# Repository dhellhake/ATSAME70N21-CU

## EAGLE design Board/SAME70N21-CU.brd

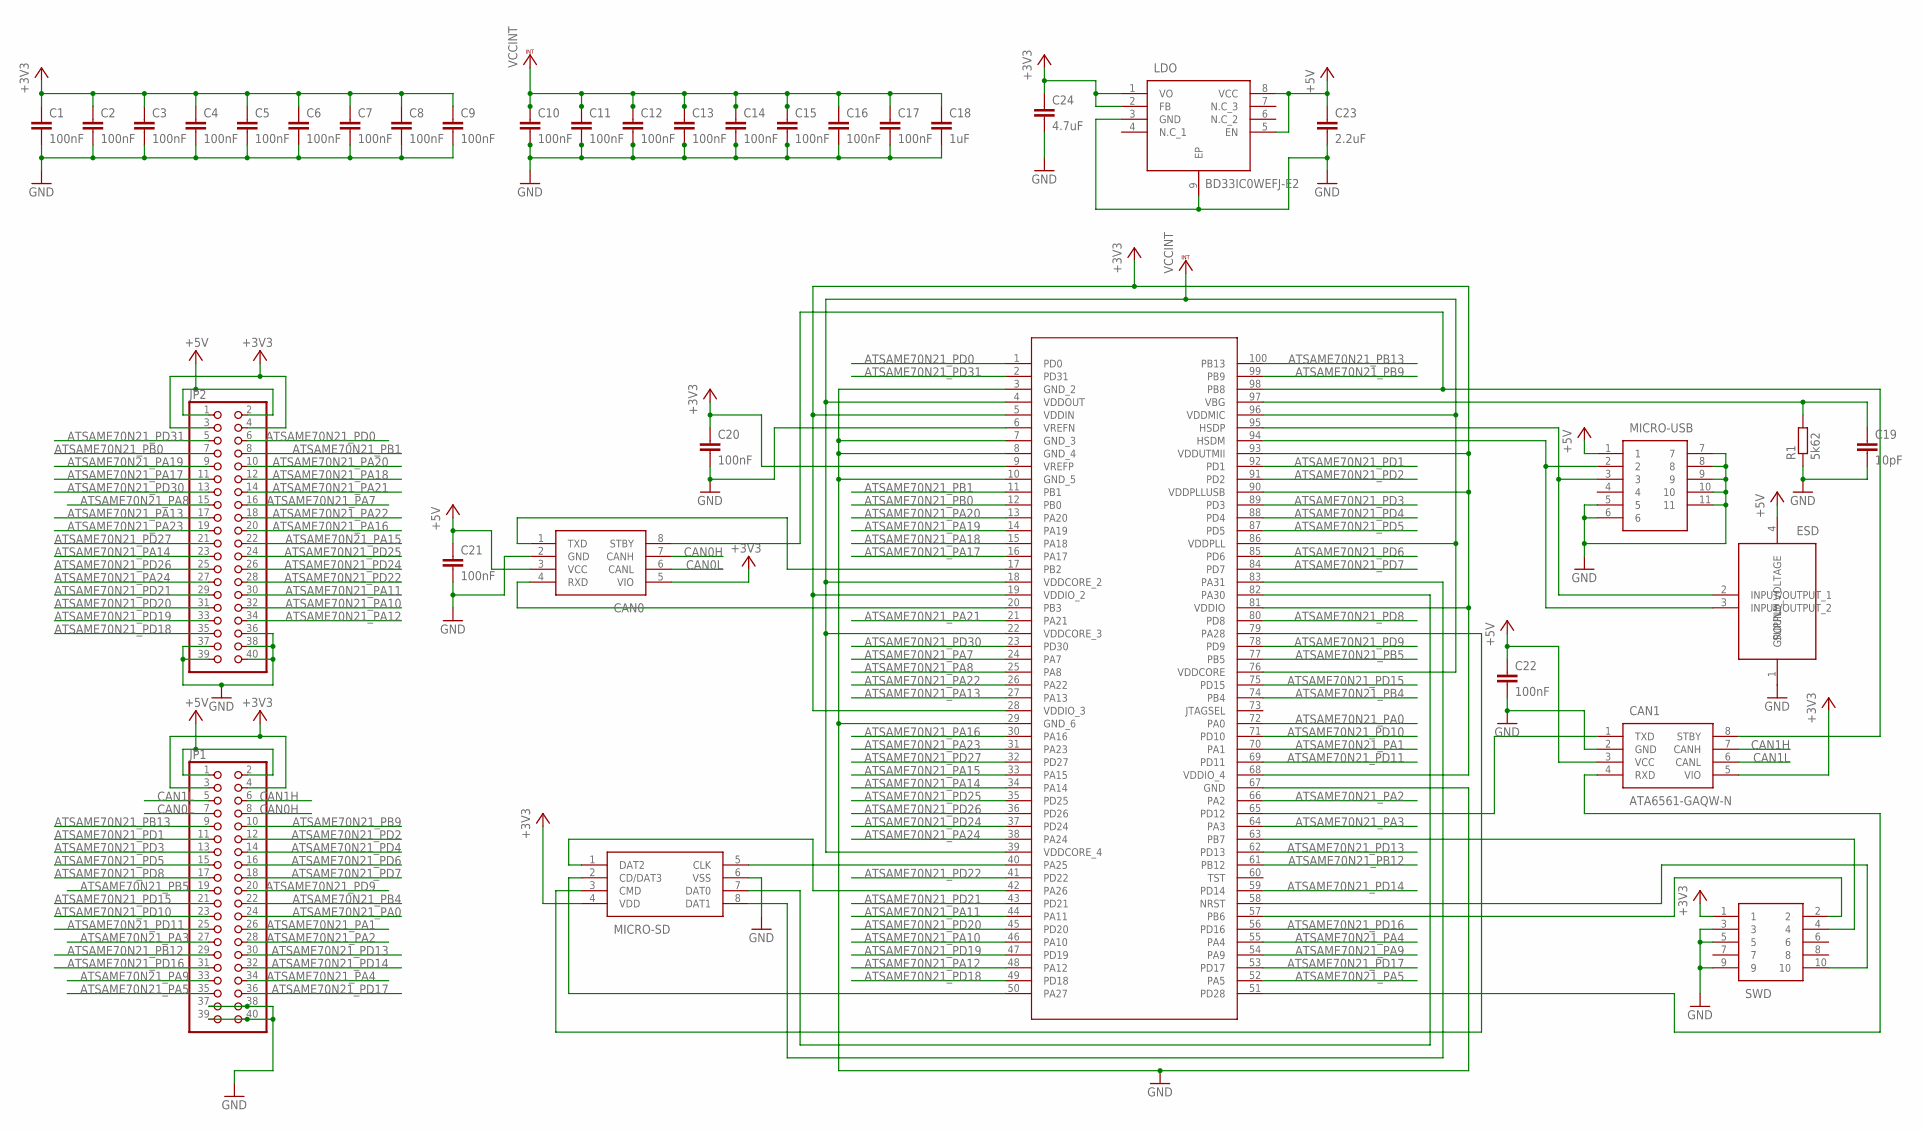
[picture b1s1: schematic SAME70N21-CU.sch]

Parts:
C1, C2, C3, C4, C5, C6, C7, C8, C9, C10, C11, C12, C13, C14, C15, C16, C17, C20, C21, C22: 100nF; C1206
C18: 1uF; C1206
C19: 10pF; C1206
C23: 2.2uF; C1206
C24: 4.7uF; C1206
CAN0, CAN1: ATA6561-GAQW-N; SOIC127P600X175-8N
ESD: PRTR5V0U2X,215; PRTR5V0U2X
JP1, JP2: PINHD-2X20; 2X20
LDO: BD33IC0WEFJ-E2; SOIC127P600X100-9N
MICRO-SD: 104031-0811; 1040310811
MICRO-USB: 10118192-0001LF; 101181920001LF
R1: 5k62; R1206
SWD: 62201021121; WURTH-1.27MM-PITCH-2WAY
U1: ATSAME70N21A-ANTQFP100_14X14MC_MCH-M; TQFP100_14X14MC_MCH-M

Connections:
+3V3: C1.1, C2.1, C3.1, C4.1, C5.1, C6.1, C7.1, C8.1, C9.1, C20.1, C24.1, CAN0.5 (VIO), CAN1.5 (VIO), JP1.3, JP1.4, JP2.3, JP2.4, LDO.1 (VO), LDO.2 (FB), MICRO-SD.4 (VDD), SWD.1, U1.5 (VDDIN), U1.9 (VREFP), U1.19 (VDDIO_2), U1.28 (VDDIO_3), U1.68 (VDDIO_4), U1.81 (VDDIO), U1.90 (VDDPLLUSB), U1.93 (VDDUTMII)
+5V: C21.1, C22.1, C23.1, CAN0.3 (VCC), CAN1.3 (VCC), ESD.4 (SUPPLY_VOLTAGE), JP1.1, JP1.2, JP2.1, JP2.2, LDO.5 (EN), LDO.8 (VCC), MICRO-USB.1
ATSAME70N21_PA0: JP1.24, U1.72 (PA0)
ATSAME70N21_PA1: JP1.26, U1.70 (PA1)
ATSAME70N21_PA2: JP1.28, U1.66 (PA2)
ATSAME70N21_PA3: JP1.27, U1.64 (PA3)
ATSAME70N21_PA4: JP1.34, U1.55 (PA4)
ATSAME70N21_PA5: JP1.35, U1.52 (PA5)
ATSAME70N21_PA7: JP2.16, U1.24 (PA7)
ATSAME70N21_PA8: JP2.15, U1.25 (PA8)
ATSAME70N21_PA9: JP1.33, U1.54 (PA9)
ATSAME70N21_PA10: JP2.32, U1.46 (PA10)
ATSAME70N21_PA11: JP2.30, U1.44 (PA11)
ATSAME70N21_PA12: JP2.34, U1.48 (PA12)
ATSAME70N21_PA13: JP2.17, U1.27 (PA13)
ATSAME70N21_PA14: JP2.23, U1.34 (PA14)
ATSAME70N21_PA15: JP2.22, U1.33 (PA15)
ATSAME70N21_PA16: JP2.20, U1.30 (PA16)
ATSAME70N21_PA17: JP2.11, U1.16 (PA17)
ATSAME70N21_PA18: JP2.12, U1.15 (PA18)
ATSAME70N21_PA19: JP2.9, U1.14 (PA19)
ATSAME70N21_PA20: JP2.10, U1.13 (PA20)
ATSAME70N21_PA21: JP2.14, U1.21 (PA21)
ATSAME70N21_PA22: JP2.18, U1.26 (PA22)
ATSAME70N21_PA23: JP2.19, U1.31 (PA23)
ATSAME70N21_PA24: JP2.27, U1.38 (PA24)
ATSAME70N21_PB0: JP2.7, U1.12 (PB0)
ATSAME70N21_PB1: JP2.8, U1.11 (PB1)
ATSAME70N21_PB4: JP1.22, U1.74 (PB4)
ATSAME70N21_PB5: JP1.19, U1.77 (PB5)
ATSAME70N21_PB9: JP1.10, U1.99 (PB9)
ATSAME70N21_PB12: JP1.29, U1.61 (PB12)
ATSAME70N21_PB13: JP1.9, U1.100 (PB13)
ATSAME70N21_PD0: JP2.6, U1.1 (PD0)
ATSAME70N21_PD1: JP1.11, U1.92 (PD1)
ATSAME70N21_PD2: JP1.12, U1.91 (PD2)
ATSAME70N21_PD3: JP1.13, U1.89 (PD3)
ATSAME70N21_PD4: JP1.14, U1.88 (PD4)
ATSAME70N21_PD5: JP1.15, U1.87 (PD5)
ATSAME70N21_PD6: JP1.16, U1.85 (PD6)
ATSAME70N21_PD7: JP1.18, U1.84 (PD7)
ATSAME70N21_PD8: JP1.17, U1.80 (PD8)
ATSAME70N21_PD9: JP1.20, U1.78 (PD9)
ATSAME70N21_PD10: JP1.23, U1.71 (PD10)
ATSAME70N21_PD11: JP1.25, U1.69 (PD11)
ATSAME70N21_PD13: JP1.30, U1.62 (PD13)
ATSAME70N21_PD14: JP1.32, U1.59 (PD14)
ATSAME70N21_PD15: JP1.21, U1.75 (PD15)
ATSAME70N21_PD16: JP1.31, U1.56 (PD16)
ATSAME70N21_PD17: JP1.36, U1.53 (PD17)
ATSAME70N21_PD18: JP2.35, U1.49 (PD18)
ATSAME70N21_PD19: JP2.33, U1.47 (PD19)
ATSAME70N21_PD20: JP2.31, U1.45 (PD20)
ATSAME70N21_PD21: JP2.29, U1.43 (PD21)
ATSAME70N21_PD22: JP2.28, U1.41 (PD22)
ATSAME70N21_PD24: JP2.26, U1.37 (PD24)
ATSAME70N21_PD25: JP2.24, U1.35 (PD25)
ATSAME70N21_PD26: JP2.25, U1.36 (PD26)
ATSAME70N21_PD27: JP2.21, U1.32 (PD27)
ATSAME70N21_PD30: JP2.13, U1.23 (PD30)
ATSAME70N21_PD31: JP2.5, U1.2 (PD31)
CAN0H: CAN0.7 (CANH), JP1.8
CAN0L: CAN0.6 (CANL), JP1.7
CAN0RX: CAN0.4 (RXD), U1.20 (PB3)
CAN0TX: CAN0.1 (TXD), U1.17 (PB2)
CAN1H: CAN1.7 (CANH), JP1.6
CAN1L: CAN1.6 (CANL), JP1.5
CAN1RX: CAN1.4 (RXD), U1.51 (PD28)
CAN1TX: CAN1.1 (TXD), U1.65 (PD12)
CAN-STBY: CAN0.8 (STBY), CAN1.8 (STBY), U1.98 (PB8)
GND: C1.2, C2.2, C3.2, C4.2, C5.2, C6.2, C7.2, C8.2, C9.2, C10.2, C11.2, C12.2, C13.2, C14.2, C15.2, C16.2, C17.2, C18.2, C19.2, C20.2, C21.2, C22.2, C23.2, C24.2, CAN0.2 (GND), CAN1.2 (GND), ESD.1 (GROUND), JP1.37, JP1.38, JP1.39, JP1.40, JP2.36, JP2.37, JP2.38, JP2.39, JP2.40, LDO.3 (GND), LDO.9 (EP), MICRO-SD.6 (VSS), MICRO-USB.5, MICRO-USB.6, MICRO-USB.7, MICRO-USB.8, MICRO-USB.9, MICRO-USB.10, MICRO-USB.11, R1.1, SWD.3, SWD.5, SWD.9, U1.3 (GND_2), U1.6 (VREFN), U1.7 (GND_3), U1.8 (GND_4), U1.10 (GND_5), U1.29 (GND_6), U1.67 (GND)
HSDM: ESD.3 (INPUT/OUTPUT_2), MICRO-USB.2, U1.94 (HSDM)
HSDP: ESD.2 (INPUT/OUTPUT_1), MICRO-USB.3, U1.95 (HSDP)
MSD-CLK: MICRO-SD.5 (CLK), U1.40 (PA25)
MSD-CMD: MICRO-SD.3 (CMD), U1.79 (PA28)
MSD-DAT0: MICRO-SD.7 (DAT0), U1.82 (PA30)
MSD-DAT1: MICRO-SD.8 (DAT1), U1.83 (PA31)
MSD-DAT2: MICRO-SD.1 (DAT2), U1.42 (PA26)
MSD-DAT3: MICRO-SD.2 (CD/DAT3), U1.50 (PA27)
NRST: SWD.10, U1.58 (NRST)
SWCLK: SWD.4, U1.63 (PB7)
SWDIO: SWD.2, U1.57 (PB6)
VBG: C19.1, R1.2, U1.97 (VBG)
VCCINT: C10.1, C11.1, C12.1, C13.1, C14.1, C15.1, C16.1, C17.1, C18.1, U1.4 (VDDOUT), U1.18 (VDDCORE_2), U1.22 (VDDCORE_3), U1.39 (VDDCORE_4), U1.76 (VDDCORE), U1.86 (VDDPLL), U1.96 (VDDMIC)

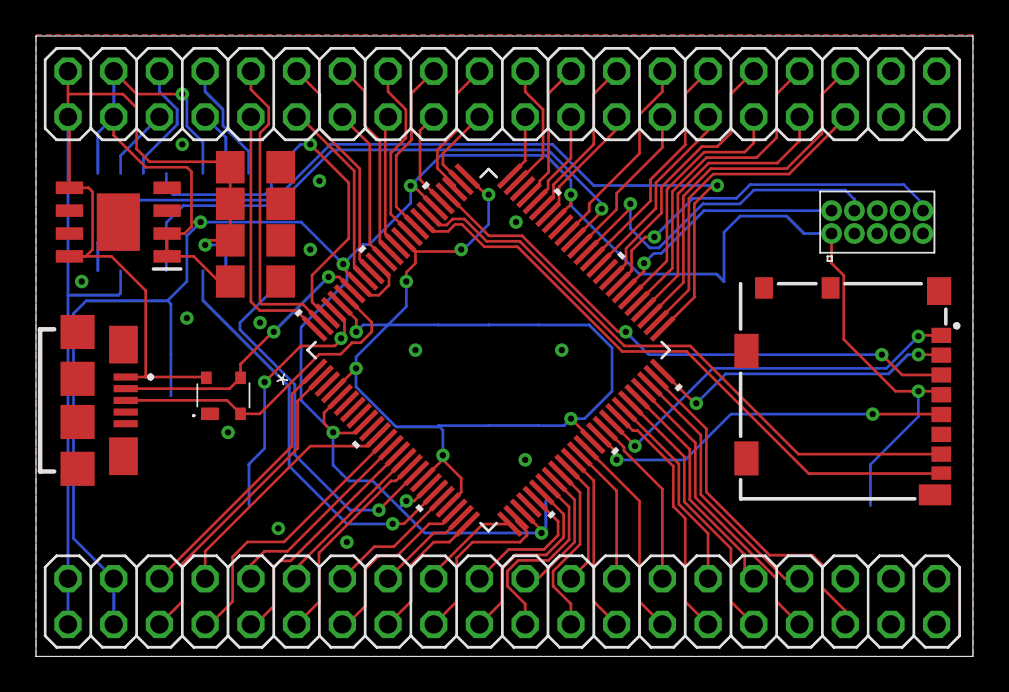
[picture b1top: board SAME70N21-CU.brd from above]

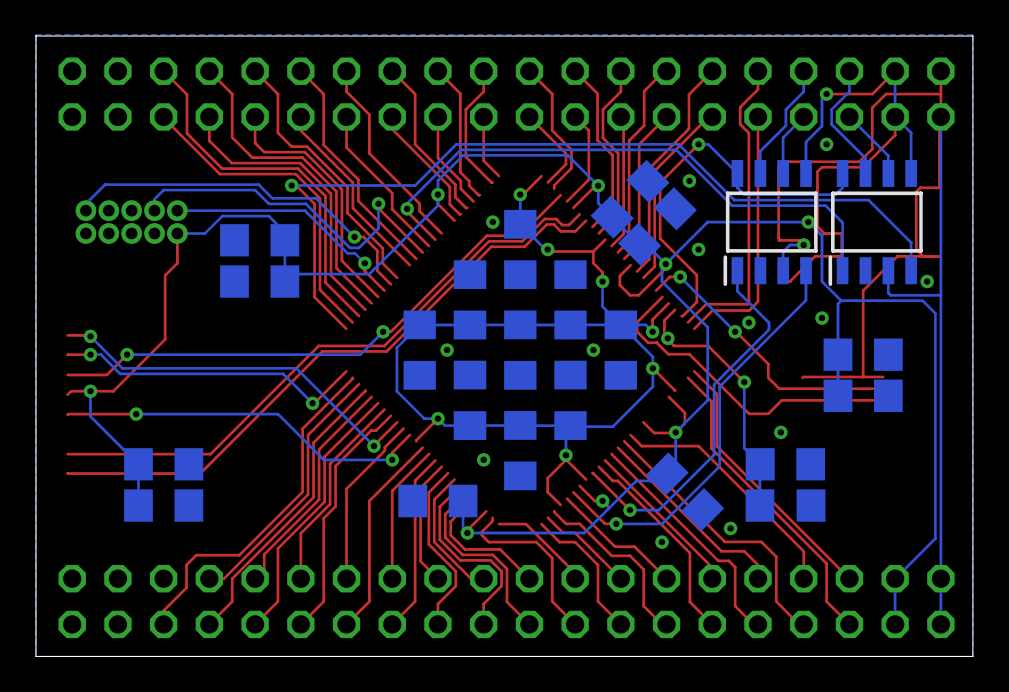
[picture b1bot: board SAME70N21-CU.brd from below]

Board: 2 copper layers, 52.0 x 34.5 mm, 35 parts (23 on the bottom side), 84 nets.

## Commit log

2022-03-18 Initial version of the custom board
    Including
    - ATSAME70N21 MCU
    - 2x CAN
    - Micro SD
    - Micro USB
2022-03-22 Major revision to first board pcb
    - reduced board size
    - fixed airwires
2022-04-01 SAME70N21-CU Board V1
    Fixed SD Card Slot orientation
2022-07-17 Added Pinout

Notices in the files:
parts and their libraries:
COPYRIGHT: Copyright (C) 2022 Ultra Librarian. All rights reserved.
